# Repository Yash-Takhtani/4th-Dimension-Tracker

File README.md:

# 4th-Dimension-Tracker
The all in one clock that has alarm, stopwatch and timer functionality which also looks really cool on the desk.

# PCB
The PCB is designed on Kicad for the following components -  
 - 6 mx style switches 
 - seeduino board 
 - buzzer 
 - TFT display.

It will be mounted with the lid of the case using 4 screws and heatset inserts.

### Schematic

### Design

### Preview

# CAD
 - For this project there are 2 things to be 3D printed, a case and a large keycap (Slightly smaller than a usual spacebar on our keyboard)

 - The case has hexagonal designs on the front and a text "4D!" which can be printed in a different colour and then stuck into the case. 

 - It consists of two parts, the lid and the base, assembled via 4 screws which also support the pcb.

 - On the sides we have triangular holes on the sides for sound to come out.

 - There are pillar like blocks inside the case to install the heatset screws.

# Firmware & Interface
The clock has a cool interface that let's you access the following menus - 

 - Home - Shows time, day and date along with a volume bar. Increase or decrease the volume with 2nd and 3rd button.
 - Stopwatch - Start or stop the stopwatch with the action button, reset with 2nd button.(sometimes won't work u may have to press multiple times)
 - Timer - Lets you set the time with 2nd,4th and 5th button. Use action button to start or dimiss timer and 3rd button to reset.(sometimes won't work u may have to press multiple times)
 - Alarm - Lets you set the specific days and time for alarm using 2nd, 3rd and 4th button. 
   - Dismiss with action button. 
   - Set 3 alarms max and configure the with button 6
   - Snooze for 5 mins via button 4 while the alarm is ringing

**You can now also set and alarm in the 4D tracker via your phone! Use [this](/alarmBLE.html) on your phone to do so via bluetooth.**

**It must be connected to wifi so that it could fetch time accurately. Therefore don't forget to add your wifi creds in the code before uploading it to the esp32 c3.**

# Build
**4D tracker has been built!**
<a href="https://youtu.be/zwGX6XkCOzQ">Check out the demo video!</a>

There were a few flaws in the CAD like the usb port was not aligned and ther space was pretty less inside for jumper cables. All these imrovements have however been made in the CAD.

I really enjoyed making this project and it is something that solves an actual problem in my life bcz I never wake up on time. 

# BOM
From the Blare kit - 
 - 1x Seeed XIAO ESP32C3
 - 6x MX-Style Keyboard Switches
 - 6x White Blank DSA Keycaps
 - 1x 2.25in TFT Screen
 - 1x 3.3V Piezo Buzzer
 - 1x 2.54mm 8 Pin Male Header
 - 8x 20cm Female-Female Jumper Wires
 - 4x M3x5x4 Heatset Inserts
 - 4x M3x8mm Screws

From the grant - 
 - 3D printed case
 - 3D printed keycap
 - PCB

# AI Usage
I mostly used google ai to help me with the firmware. The ringtone that plays when the alarm rings is also generated by AI. Sometimes to help me with basic things like navigating around in kicad or fusion and searching up things when I got stuck.

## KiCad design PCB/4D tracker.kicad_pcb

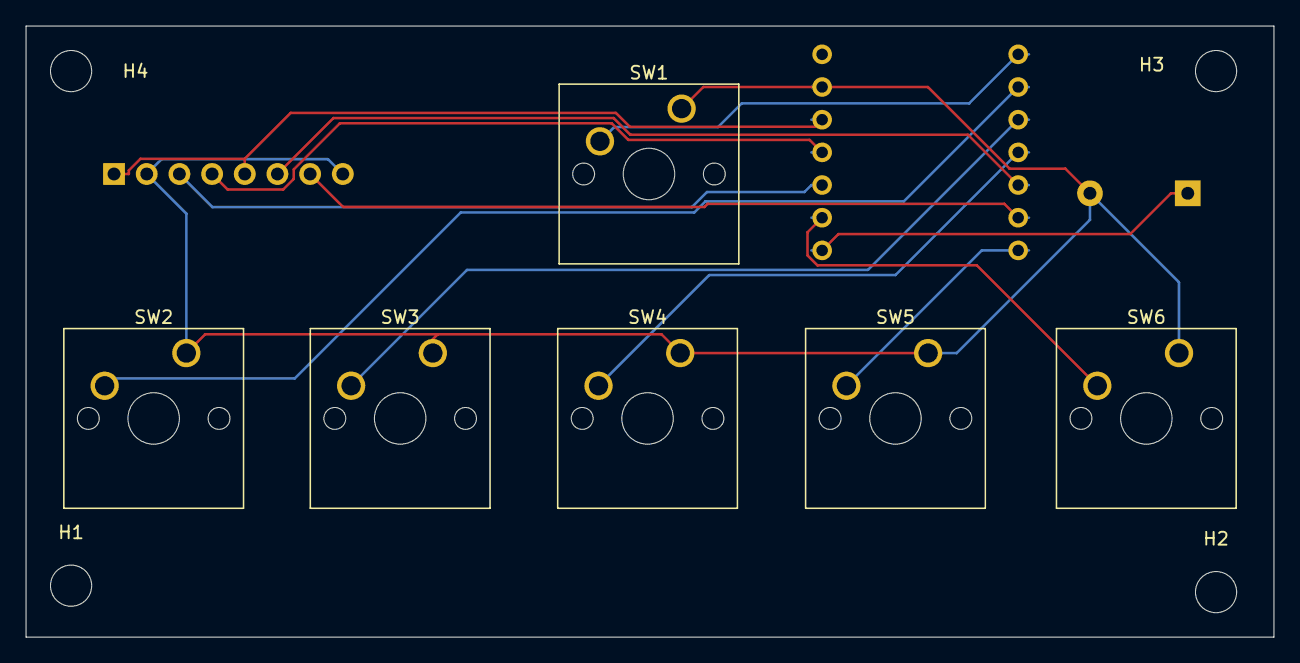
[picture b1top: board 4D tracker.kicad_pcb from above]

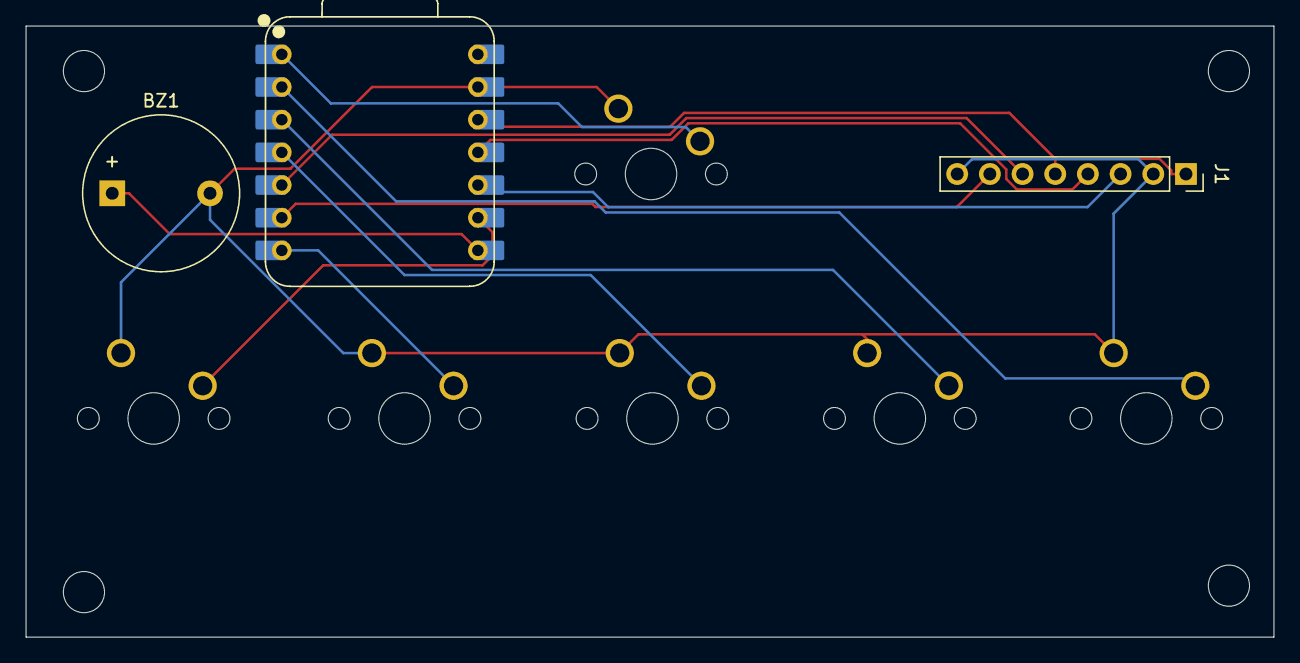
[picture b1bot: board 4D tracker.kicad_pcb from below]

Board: 2 copper layers, 97.0 x 47.5 mm, 13 parts (3 on the bottom side), 13 nets.

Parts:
BZ1: Buzzer; Buzzer_12x9.5RM7.6
H1, H2, H3, H4: MountingHole; MountingHole_3.2mm_M3
J1: Conn_01x08_Pin; PinSocket_1x08_P2.54mm_Vertical
SW1, SW2, SW3, SW4, SW5, SW6: SW_Push; SW_Cherry_MX_1.00u_PCB
U1: XIAO-ESP32-C3-SMD; XIAO-ESP32-C3-DIP

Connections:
+3V3: J1.1, J1.5, U1.12 (3V3_OUT)
/cs: J1.7, U1.6 (D5)
/dc: J1.6, U1.5 (D4)
/scl: J1.3, U1.10 (D9/BOOT)
/sda: J1.4, U1.11 (D10)
GND: BZ1.2 (-), J1.2, J1.8, SW1.1, SW2.1, SW3.1, SW4.1, SW5.1, SW6.1, U1.13 (GND)
unnamed: BZ1.1 (+), U1.8 (D7)
unnamed: SW1.2, U1.1 (D0)
unnamed: SW2.2, U1.2 (D1)
unnamed: SW3.2, U1.3 (D2)
unnamed: SW4.2, U1.4 (D3)
unnamed: SW5.2, U1.7 (D6)
unnamed: SW6.2, U1.9 (D8)
